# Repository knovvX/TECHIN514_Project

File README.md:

# TECHIN514_Project

`Diyun Lu 2430741`

### Sonic Flow - A Music Visualization Device

#### Overview

Sonic Flow senses the music around and visualize the waveform. The sensing device is responsible for detecting the music around. And the display device will display the corresponding waveforms together with a part acting as a monotrome to display the bpm.

#### Sensing Device

The sensing device is equipped with a microphone sensor, which is recording the sound waves and send it to display device. A bluetooth module of esp32 will handle this transmission, since in the application, these two devices should not be very far, so I chose bluetooth. Also the sound level will affect the brightness of the LED strip around the cube, louder the sound is, brighter the LED is.

#### Display Device

The display device is mainly displaying the waveform and the bpm of the music detected. BPM is displayed through the stepper-motor-driven gauge needle as a monotrome. Further ML will be embedded on the microncontroller to detect the emotion of the music and also display it on the OLED. A design of different kinds of waveforms will be enabled by a button to switch between different designs.

#### Connection Diagram

The connection of the two parts are shown below. They connect with each other through ESP32's Bluetooth module. And ESP32 is responsible for the control of other sensors.

#### Device Composition

| Device          | Sensor / Element                                             | Functionality                     |
| --------------- | ------------------------------------------------------------ | --------------------------------- |
| Sensing         | SPH0645LM4H-B                                                | Microphone                        |
| Sensing         | 3.7V / ++?                                                   | Battery                           |
| Display         | 3.7V / ++?                                                   | Battery                           |
| Display         | SSD1305(Long, for waves),https://www.adafruit.com/product/292,Adafruit OLED FeatherWing(Small, for displaying bpm) | OLED                              |
| Display         | D6R90 F2 LFS                                                 | Button                            |
| Display/Sensing | RGB                                                          | LED                               |
| Display         | https://www.adafruit.com/product/2424                        | Stepper-motor-driven Gauge Needle |
|                 | ESP32                                                        | Bluetooth and control             |

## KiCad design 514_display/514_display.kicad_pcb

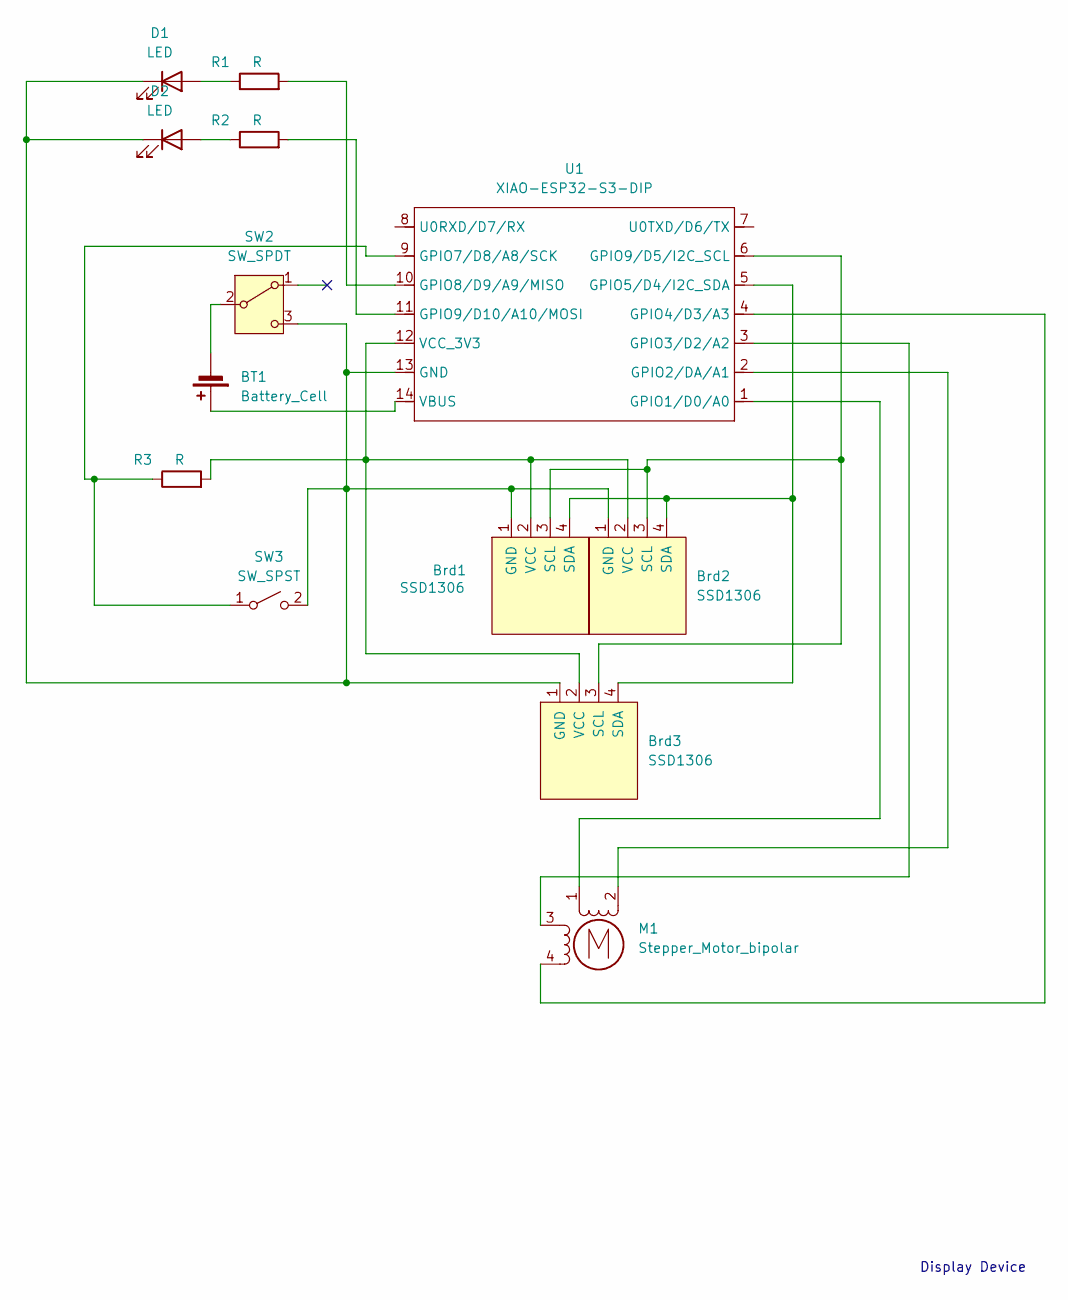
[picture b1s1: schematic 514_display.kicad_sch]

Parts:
BT1: Battery_Cell; JST_JWPF_B02B-JWPF-SK-R_1x02_P2.00mm_Vertical
Brd1, Brd2, Brd3: SSD1306; 128x64OLED
D1, D2: LED; LED_D5.0mm
M1: Stepper_Motor_bipolar; x27_stepper_two_holes
R1, R2, R3: R; R_0805_2012Metric_Pad1.20x1.40mm_HandSolder
SW2: SW_SPDT; PinHeader_1x03_P2.54mm_Vertical
SW3: SW_SPST; SW_PUSH-12mm
U1: XIAO-ESP32-S3-DIP; XIAO-ESP32S3-DIP

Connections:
unnamed: BT1.1 (+), U1.14 (VBUS)
unnamed: BT1.2 (-), SW2.2 (B)
unnamed: Brd1.1 (GND), Brd2.1 (GND), Brd3.1 (GND), D1.1 (K), D2.1 (K), SW2.3 (C), SW3.2 (B), U1.13 (GND)
unnamed: Brd1.3 (SCL), Brd2.3 (SCL), Brd3.3 (SCL), U1.6 (GPIO9/D5/I2C_SCL)
unnamed: Brd1.4 (SDA), Brd2.4 (SDA), Brd3.4 (SDA), U1.5 (GPIO5/D4/I2C_SDA)
unnamed: Brd1.2 (VCC), Brd2.2 (VCC), Brd3.2 (VCC), R3.2, U1.12 (VCC_3V3)
unnamed: D1.2 (A), R1.1
unnamed: D2.2 (A), R2.1
unnamed: M1.2 (-), U1.2 (GPIO2/DA/A1)
unnamed: R3.1, SW3.1 (A), U1.9 (GPIO7/D8/A8/SCK)
unnamed: M1.1, U1.1 (GPIO1/D0/A0)
unnamed: M1.3, U1.3 (GPIO3/D2/A2)
unnamed: M1.4, U1.4 (GPIO4/D3/A3)
unnamed: R1.2, U1.10 (GPIO8/D9/A9/MISO)
unnamed: R2.2, U1.11 (GPIO9/D10/A10/MOSI)

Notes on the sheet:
Display Device

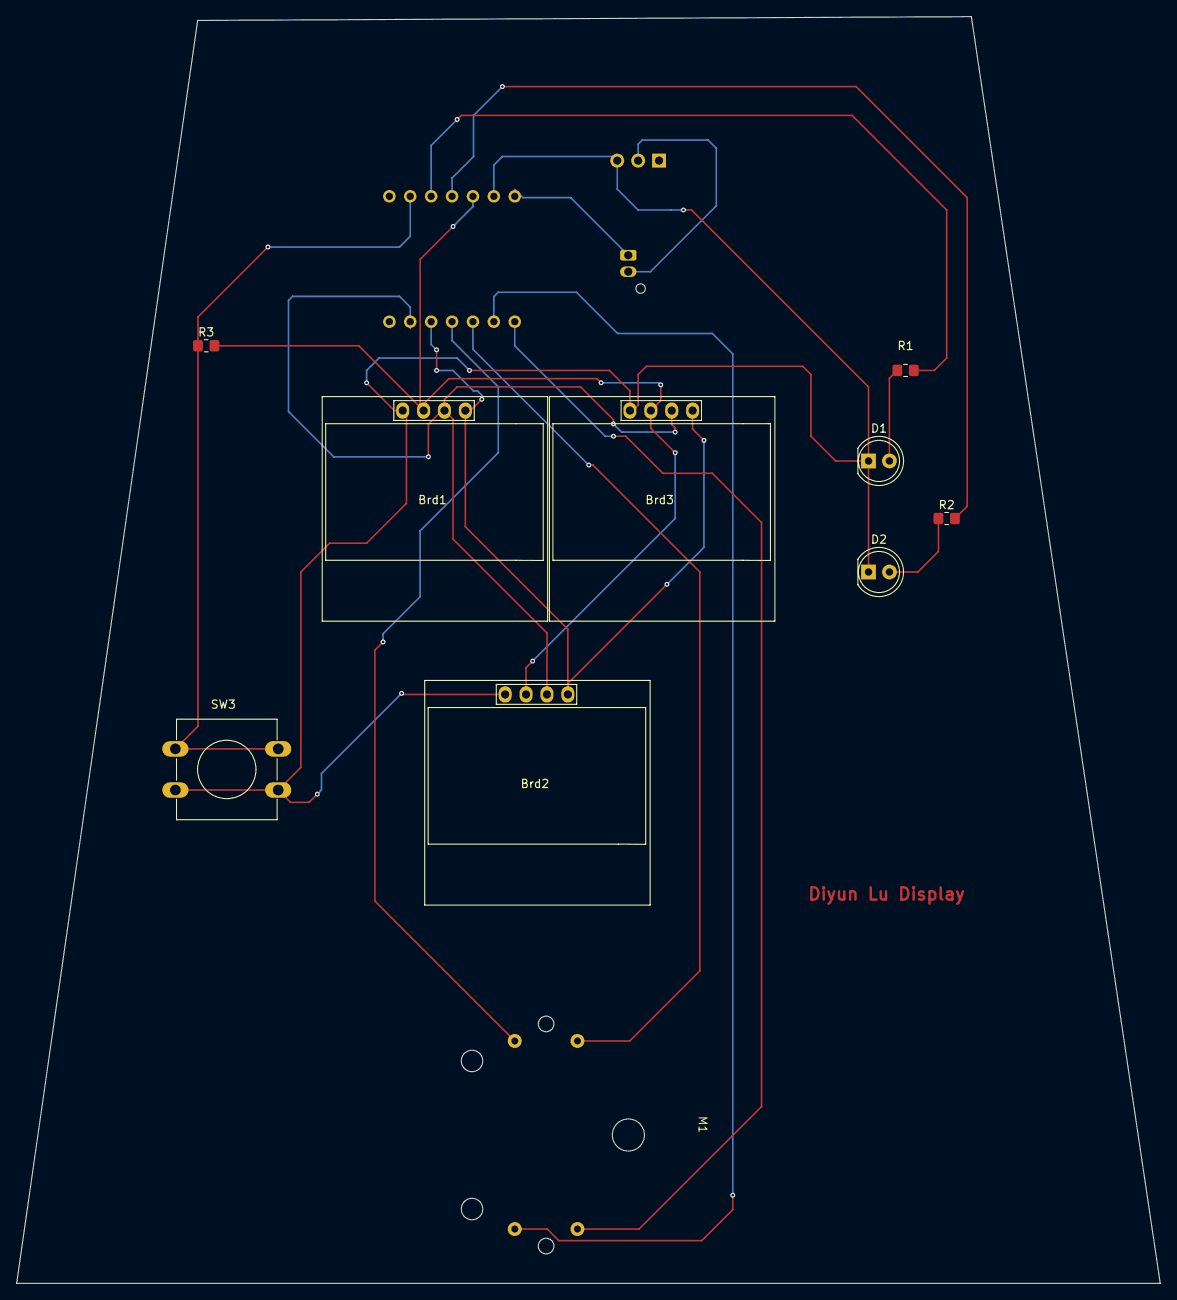
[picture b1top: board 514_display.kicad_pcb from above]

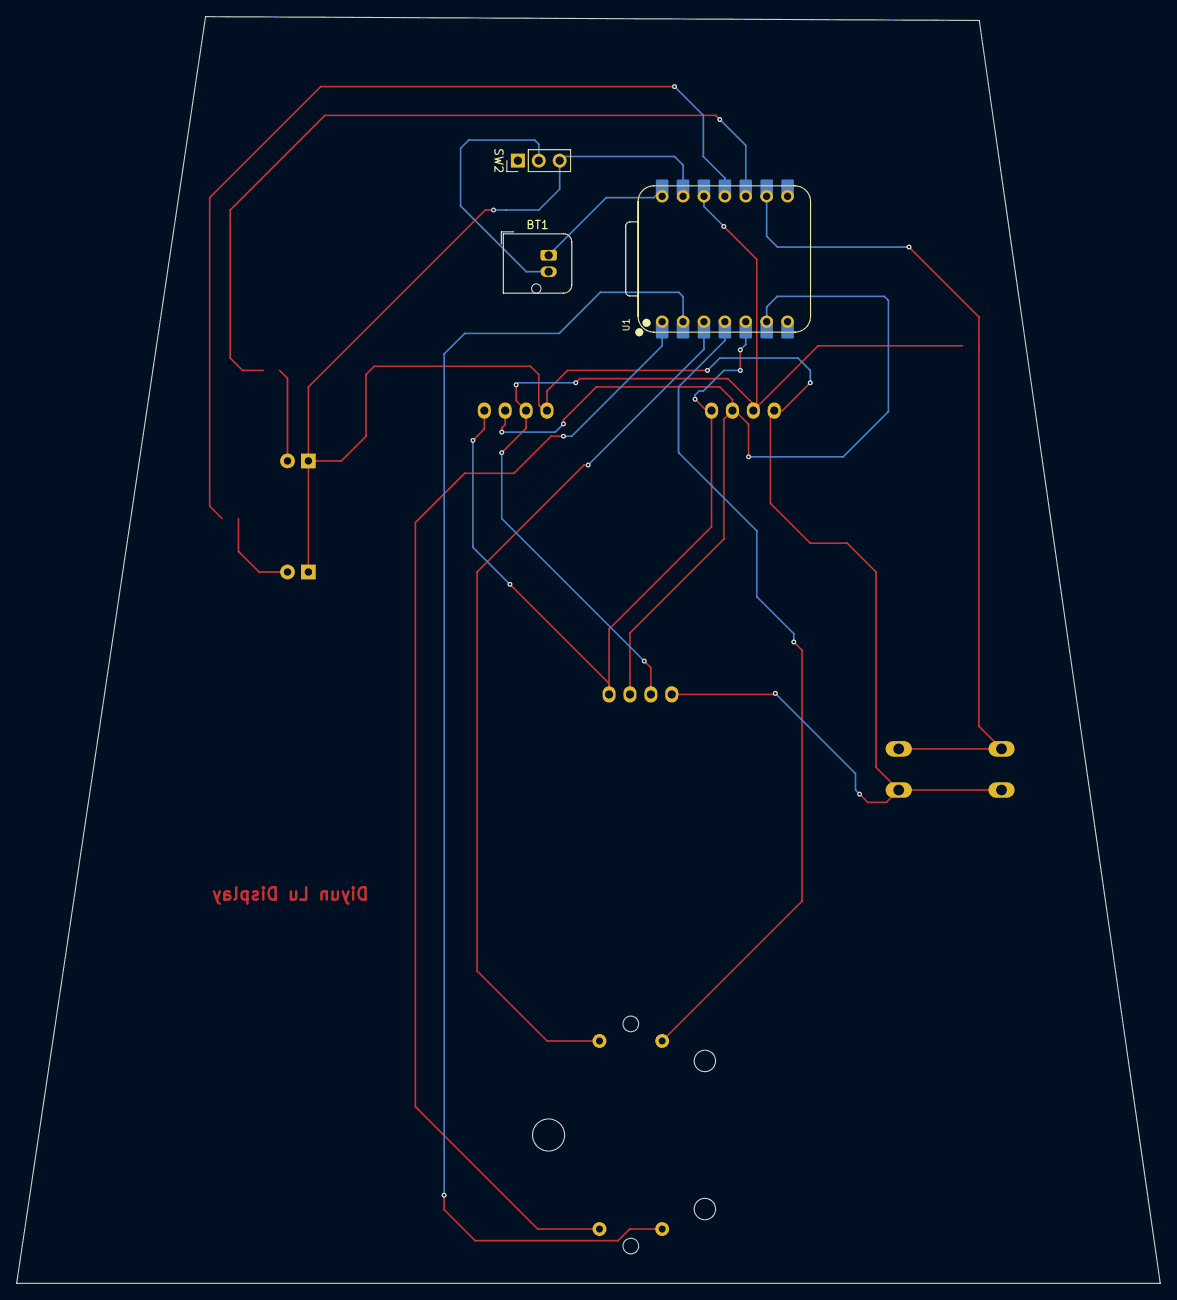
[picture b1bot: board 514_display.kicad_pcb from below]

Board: 2 copper layers, 139.0 x 154.0 mm, 13 parts (3 on the bottom side), 15 nets.

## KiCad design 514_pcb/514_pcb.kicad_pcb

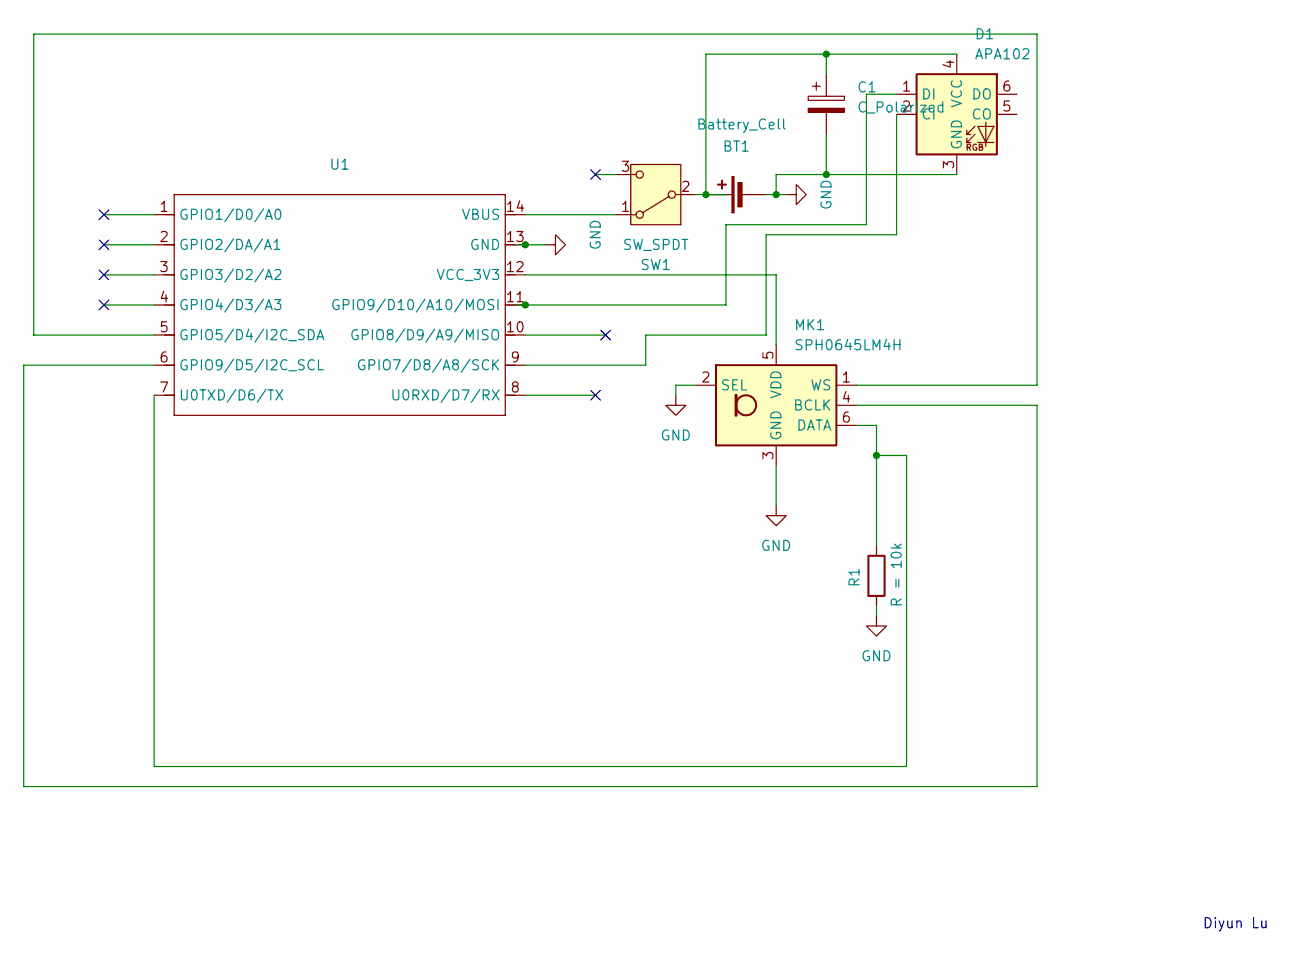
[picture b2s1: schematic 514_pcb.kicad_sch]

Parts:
BT1: Battery_Cell; JST_JWPF_B02B-JWPF-SK-R_1x02_P2.00mm_Vertical
C1: C_Polarized; R_0603_1608Metric_Pad0.98x0.95mm_HandSolder
D1: APA102; LED_RGB_5050-6
MK1: SPH0645LM4H; Knowles_SPH0645LM4H-6_3.5x2.65mm
R1: R = 10k; R_0603_1608Metric_Pad0.98x0.95mm_HandSolder
SW1: SW_SPDT; PinHeader_1x03_P2.54mm_Vertical
U1: XIAO-ESP32S3-DIP

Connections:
GND: BT1.2 (-), C1.2, D1.3 (GND), MK1.2 (SEL), MK1.3 (GND), R1.2, U1.13 (GND)
unnamed: BT1.1 (+), C1.1, D1.4 (VCC), SW1.2 (B)
unnamed: D1.2 (CI), U1.9 (GPIO7/D8/A8/SCK)
unnamed: D1.1 (DI), U1.11 (GPIO9/D10/A10/MOSI)
unnamed: MK1.4 (BCLK), U1.6 (GPIO9/D5/I2C_SCL)
unnamed: MK1.6 (DATA), R1.1, U1.7 (U0TXD/D6/TX)
unnamed: MK1.5 (VDD), U1.12 (VCC_3V3)
unnamed: MK1.1 (WS), U1.5 (GPIO5/D4/I2C_SDA)
unnamed: SW1.1 (A), U1.14 (VBUS)

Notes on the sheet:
Diyun Lu

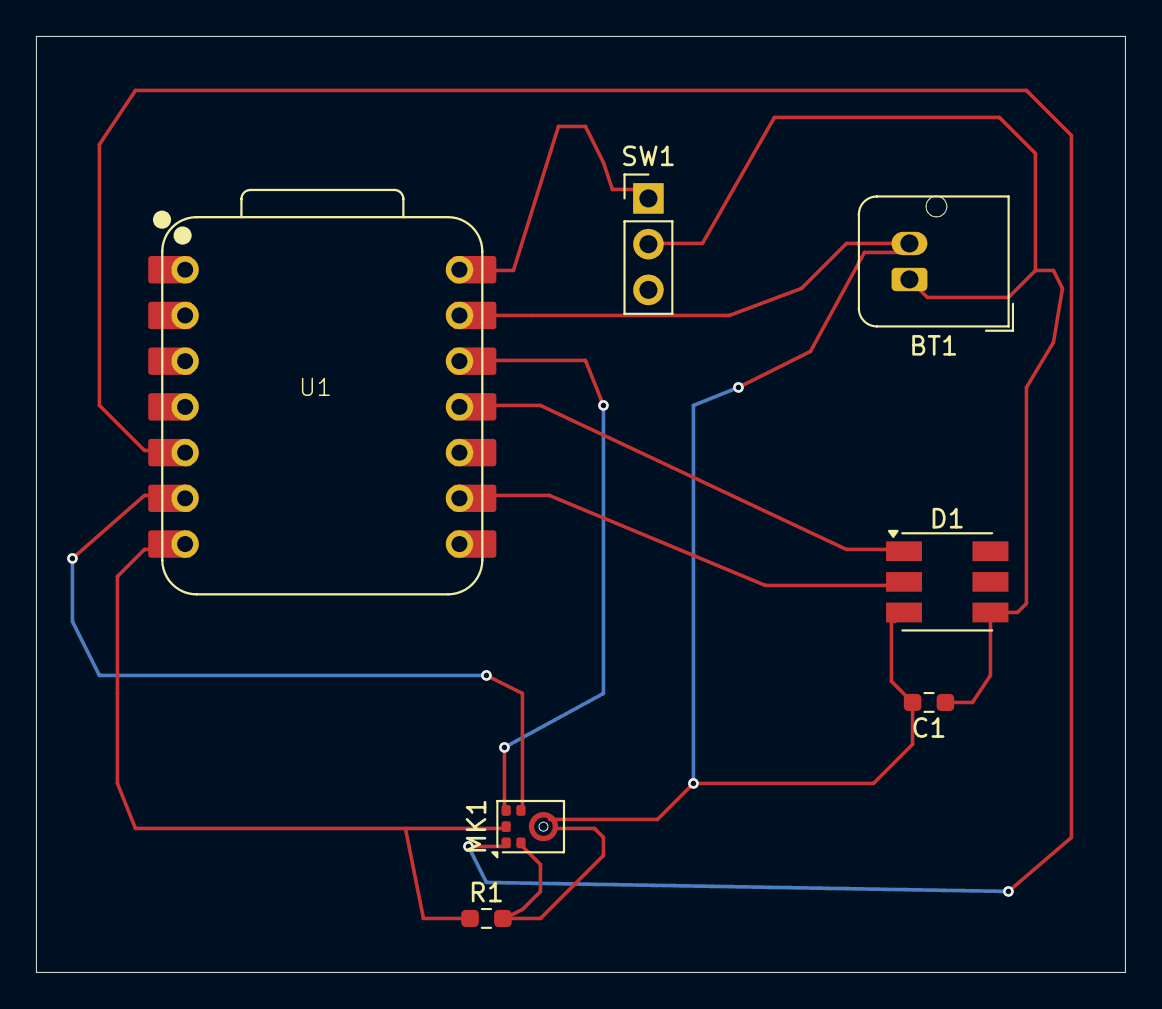
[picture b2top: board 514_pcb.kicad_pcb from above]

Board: 2 copper layers, 60.5 x 52.0 mm, 7 parts (0 on the bottom side), 9 nets.

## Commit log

2025-01-21 update: initial drafts
2025-01-22 update: diagram added
2025-01-22 fix: images direction
2025-01-28 update: pcb
2025-02-13 update power spreadsheet
2025-02-13 update spread sheet
2025-03-03 display update
2025-03-04 update 3d print files
2025-03-09 update arduino test codes
2025-03-10 code uploaded
